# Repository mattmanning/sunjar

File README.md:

http://mwmanning.com/2013/03/31/Sun-Jar-Prototyping.html

Buy the latest version [here](http://oshpark.com/shared_projects/m9a7AydS).

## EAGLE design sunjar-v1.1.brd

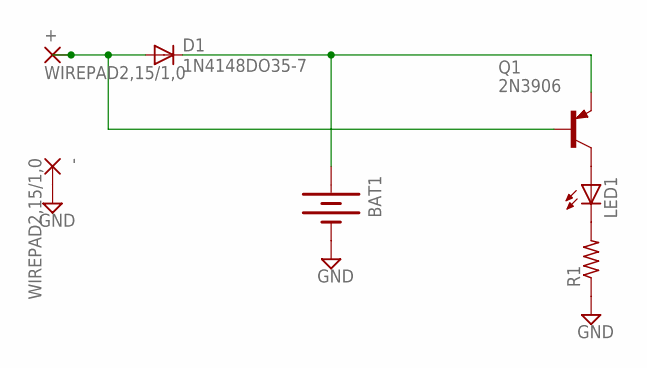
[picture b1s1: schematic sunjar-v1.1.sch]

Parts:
+: WIREPAD2,15/1,0; 2,15/1,0
-: WIREPAD2,15/1,0; 2,15/1,0
BAT1: BATTERY245PTH; BATTCON_245MM_PTH
D1: 1N4148DO35-7; DO35-7
LED1: LED5MM
Q1: 2N3906; TO92
R1: R-US_0207/10; 0207/10

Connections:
GND: -.1, BAT1.2 (-), R1.1
unnamed: LED1.K (C), R1.2
unnamed: LED1.A, Q1.1 (C)
unnamed: +.1, D1.A, Q1.2 (B)
unnamed: BAT1.3 (+), D1.C, Q1.3 (E)

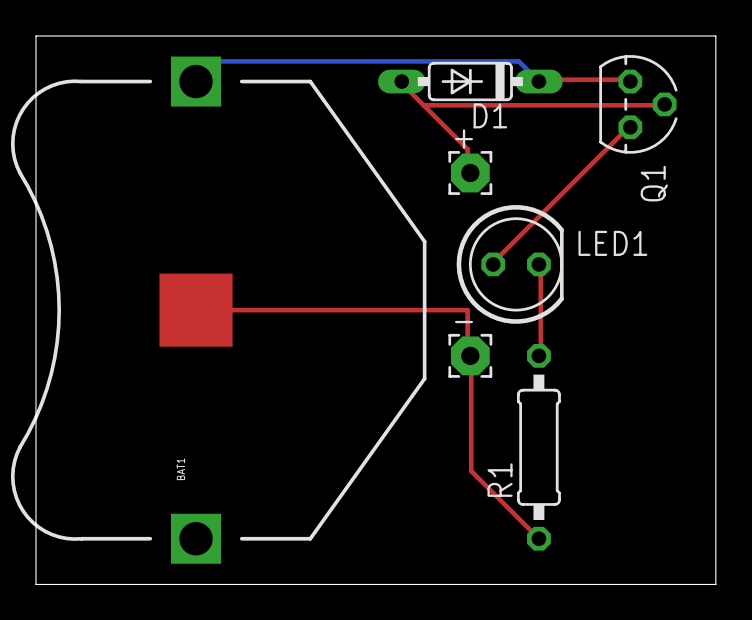
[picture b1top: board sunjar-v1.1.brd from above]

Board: 2 copper layers, 37.8 x 30.5 mm, 7 parts (0 on the bottom side), 5 nets.

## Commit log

2013-04-01 Eagle schematic and board layout.
2013-08-11 Share Gerber files.
2013-08-11 Use raw link.
2013-08-11 v1.1 files and README update.

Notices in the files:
parts and their libraries:
SparkFun-Electromechanical: Licensing: CC v3.0 Share-Alike You are welcome to use this library for commercial purposes.
